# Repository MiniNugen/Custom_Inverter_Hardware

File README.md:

# Custom_Inverter_Hardware
## File Tree Should be organized like so:

PCB_Project_Name_REV1.PrjPCB  
|  Source Documents  
|  |  PCB_Project_Name_REV1.SchDOC  
|  |  PCB_Project_Name_REV1.PcbDOC  
|  |  BOM  
|  Settings  
|  Libraries  

PCB_Project_Name_REV2.PrjPCB  
|  Source Documents  
|  |  PCB_Project_Name_REV2.SchDOC  
|  |  PCB_Project_Name_REV2.PcbDOC  
|  |  BOM  
|  Settings  
|  Libraries  

PCB_Project_Name_REV3.PrjPCB  
|  Source Documents  
|  |  PCB_Project_Name_REV3.SchDOC  
|  |  PCB_Project_Name_REV3.PcbDOC  
|  |  BOM  
|  Settings  
|  Libraries

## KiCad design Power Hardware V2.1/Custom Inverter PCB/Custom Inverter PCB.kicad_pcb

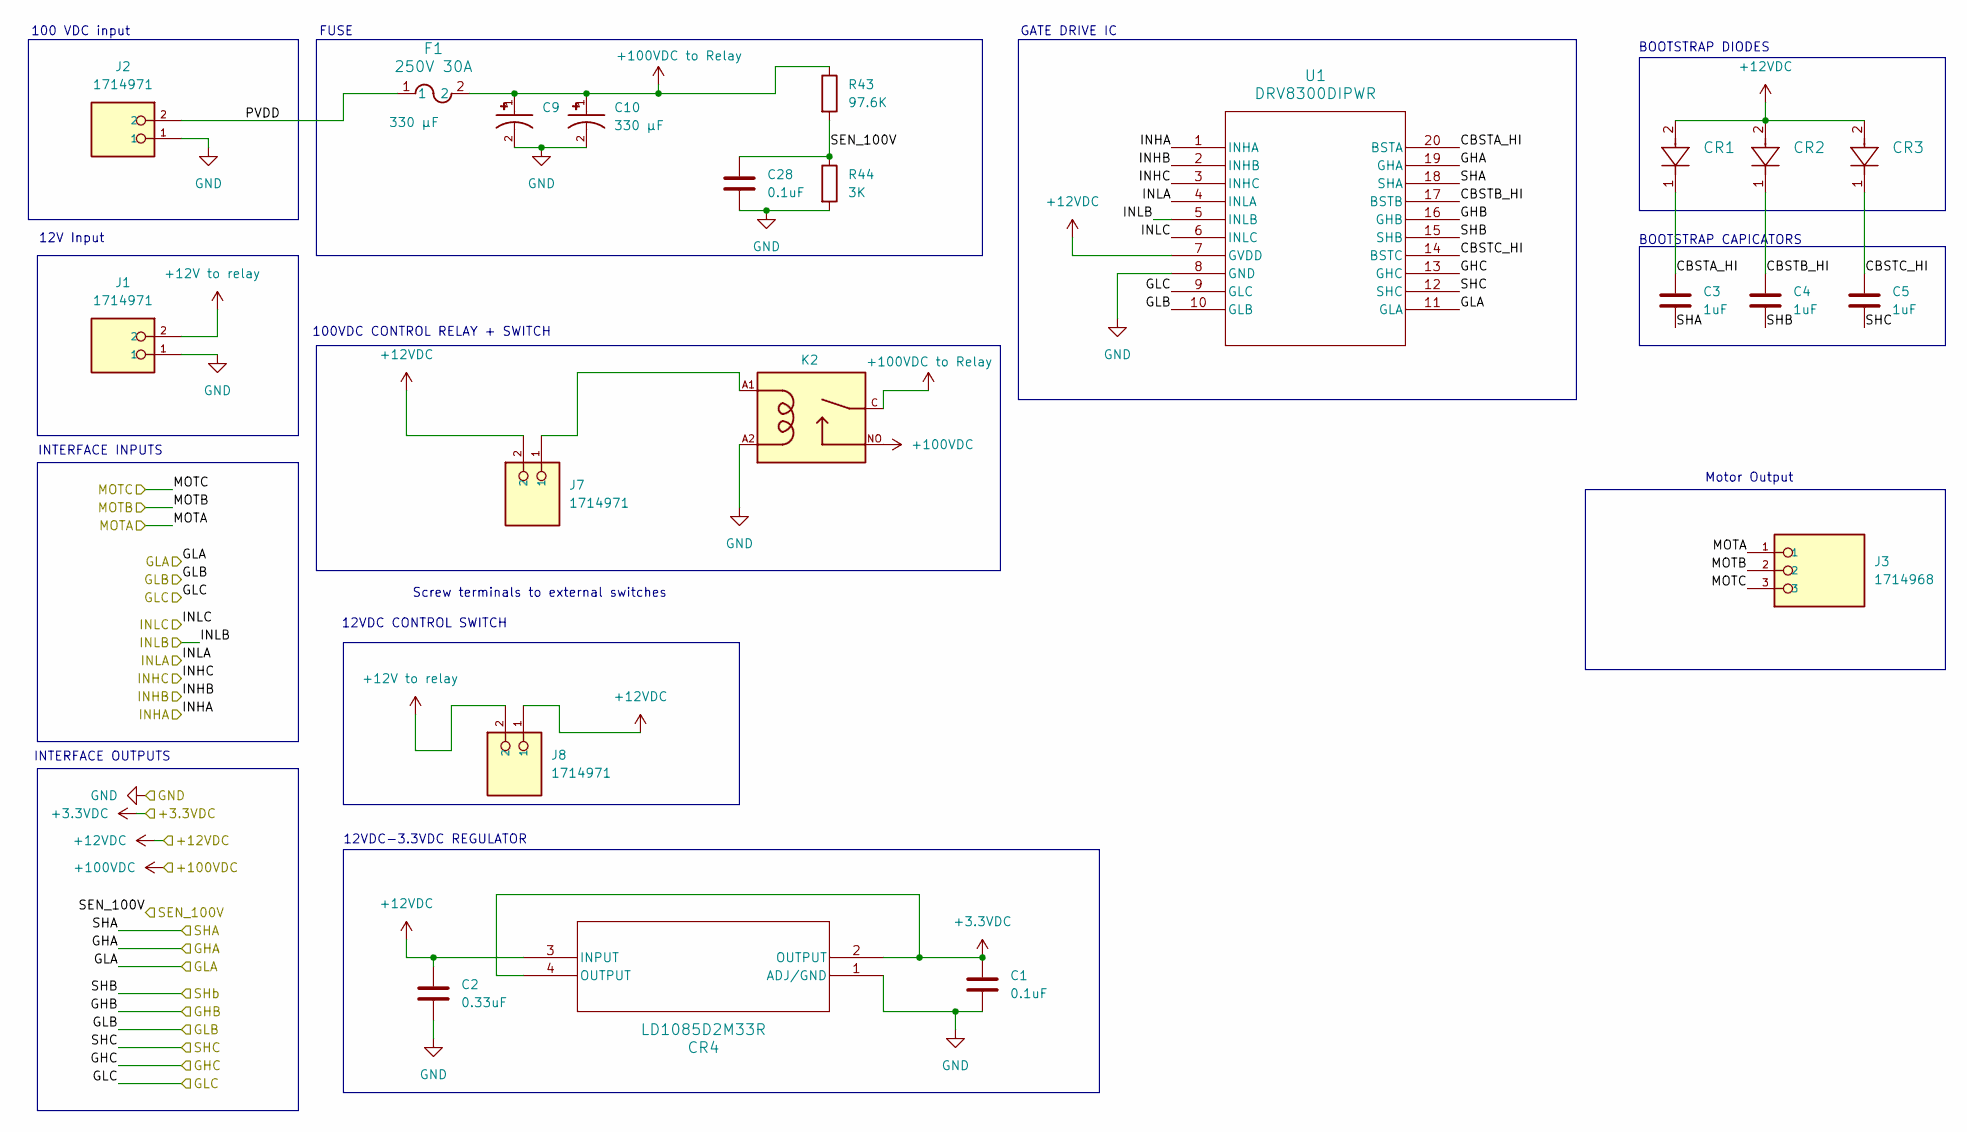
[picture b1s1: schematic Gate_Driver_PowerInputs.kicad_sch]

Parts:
C1: 0.1uF; C_0805_2012Metric; Part Number 0805ZD104KAT2A
C2: 0.33uF; C_0805_2012Metric; Part Number GRM219R71H334KA88D
C3, C4, C5: 1uF; C_0805_2012Metric; Part Number CL21B105KBFNFNE
C9, C10: 330 µF; CAP_EEVFK2A331M; PARTREV 10-Oct-19
C28: 0.1uF; C_0805_2012Metric; Part Number CC0805KRX7R9BB104
CR1, CR2, CR3: CR_SOD-323_MCC; Part Number BAV20WS-TP
CR4: LD1085D2M33R; D2PAK&slash_A_STM; Part Number LD1085D2M33R
F1: 250V 30A; FUSE_0463_LTF-M; Part Number 0463030.ER
J1, J2, J7, J8: 1714971; PHOENIX_1714971; PARTREV 26.05.2020
J3: 1714968; PHOENIX_1714968; Part Number 1714968
K2: 1-1393210-3; TE_1-1393210-3; PARTREV 0815
R43: 97.6K; R_0805_2012Metric; Part Number RC0805FR-0797K6L
R44: 3K; R_0805_2012Metric; Part Number CRG0805F3K0
U1: DRV8300DIPWR; TSSOP_0DIPWR_TEX; Part Number DRV8300DIPWR

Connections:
+3.3V: C1.1, CR4.2 (OUTPUT), CR4.4 (OUTPUT); also elsewhere on the board
+12V to relay: J1.2, J8.2
+12VDC: C2.1, CR1.2, CR2.2, CR3.2, CR4.3 (INPUT), J7.2, J8.1, U1.7 (GVDD)
+100VDC: K2.NO; also elsewhere on the board
+100VDC to Relay: C9.1, C10.1, F1.2, K2.C, R43.1
/GateDriver&Power Inputs/CBSTA_HI: C3.1, CR1.1, U1.20 (BSTA)
/GateDriver&Power Inputs/CBSTB_HI: C4.1, CR2.1, U1.17 (BSTB)
/GateDriver&Power Inputs/CBSTC_HI: C5.1, CR3.1, U1.14 (BSTC)
/GateDriver&Power Inputs/GHA: U1.19 (GHA); also elsewhere on the board
/GateDriver&Power Inputs/GHB: U1.16 (GHB); also elsewhere on the board
/GateDriver&Power Inputs/GHC: U1.13 (GHC); also elsewhere on the board
/GateDriver&Power Inputs/GLA: U1.11 (GLA); also elsewhere on the board
/GateDriver&Power Inputs/GLB: U1.10 (GLB); also elsewhere on the board
/GateDriver&Power Inputs/GLC: U1.9 (GLC); also elsewhere on the board
/GateDriver&Power Inputs/PVDD: F1.1, J2.2
/INHA: U1.1 (INHA); also elsewhere on the board
/INHB: U1.2 (INHB); also elsewhere on the board
/INHC: U1.3 (INHC); also elsewhere on the board
/INLA: U1.4 (INLA); also elsewhere on the board
/INLB: U1.5 (INLB); also elsewhere on the board
/INLC: U1.6 (INLC); also elsewhere on the board
/MOTA: J3.1; also elsewhere on the board
/MOTB: J3.2; also elsewhere on the board
/MOTC: J3.3; also elsewhere on the board
/SEN_100V: C28.1, R43.2, R44.1; also elsewhere on the board
/SHA: C3.2, U1.18 (SHA); also elsewhere on the board
/SHB: C4.2, U1.15 (SHB); also elsewhere on the board
/SHC: C5.2, U1.12 (SHC); also elsewhere on the board
GND: C1.2, C2.2, C9.2, C10.2, C28.2, CR4.1 (ADJ/GND), J1.1, J2.1, K2.A2, R44.2, U1.8 (GND); also elsewhere on the board
unnamed: J7.1, K2.A1

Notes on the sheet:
100VDC CONTROL RELAY + SWITCH
Motor Output
100 VDC input
12VDC-3.3VDC REGULATOR
12V Input
Screw terminals to external switches
FUSE
12VDC CONTROL SWITCH
GATE DRIVE IC
INTERFACE INPUTS
BOOTSTRAP DIODES
BOOTSTRAP CAPICATORS
INTERFACE OUTPUTS

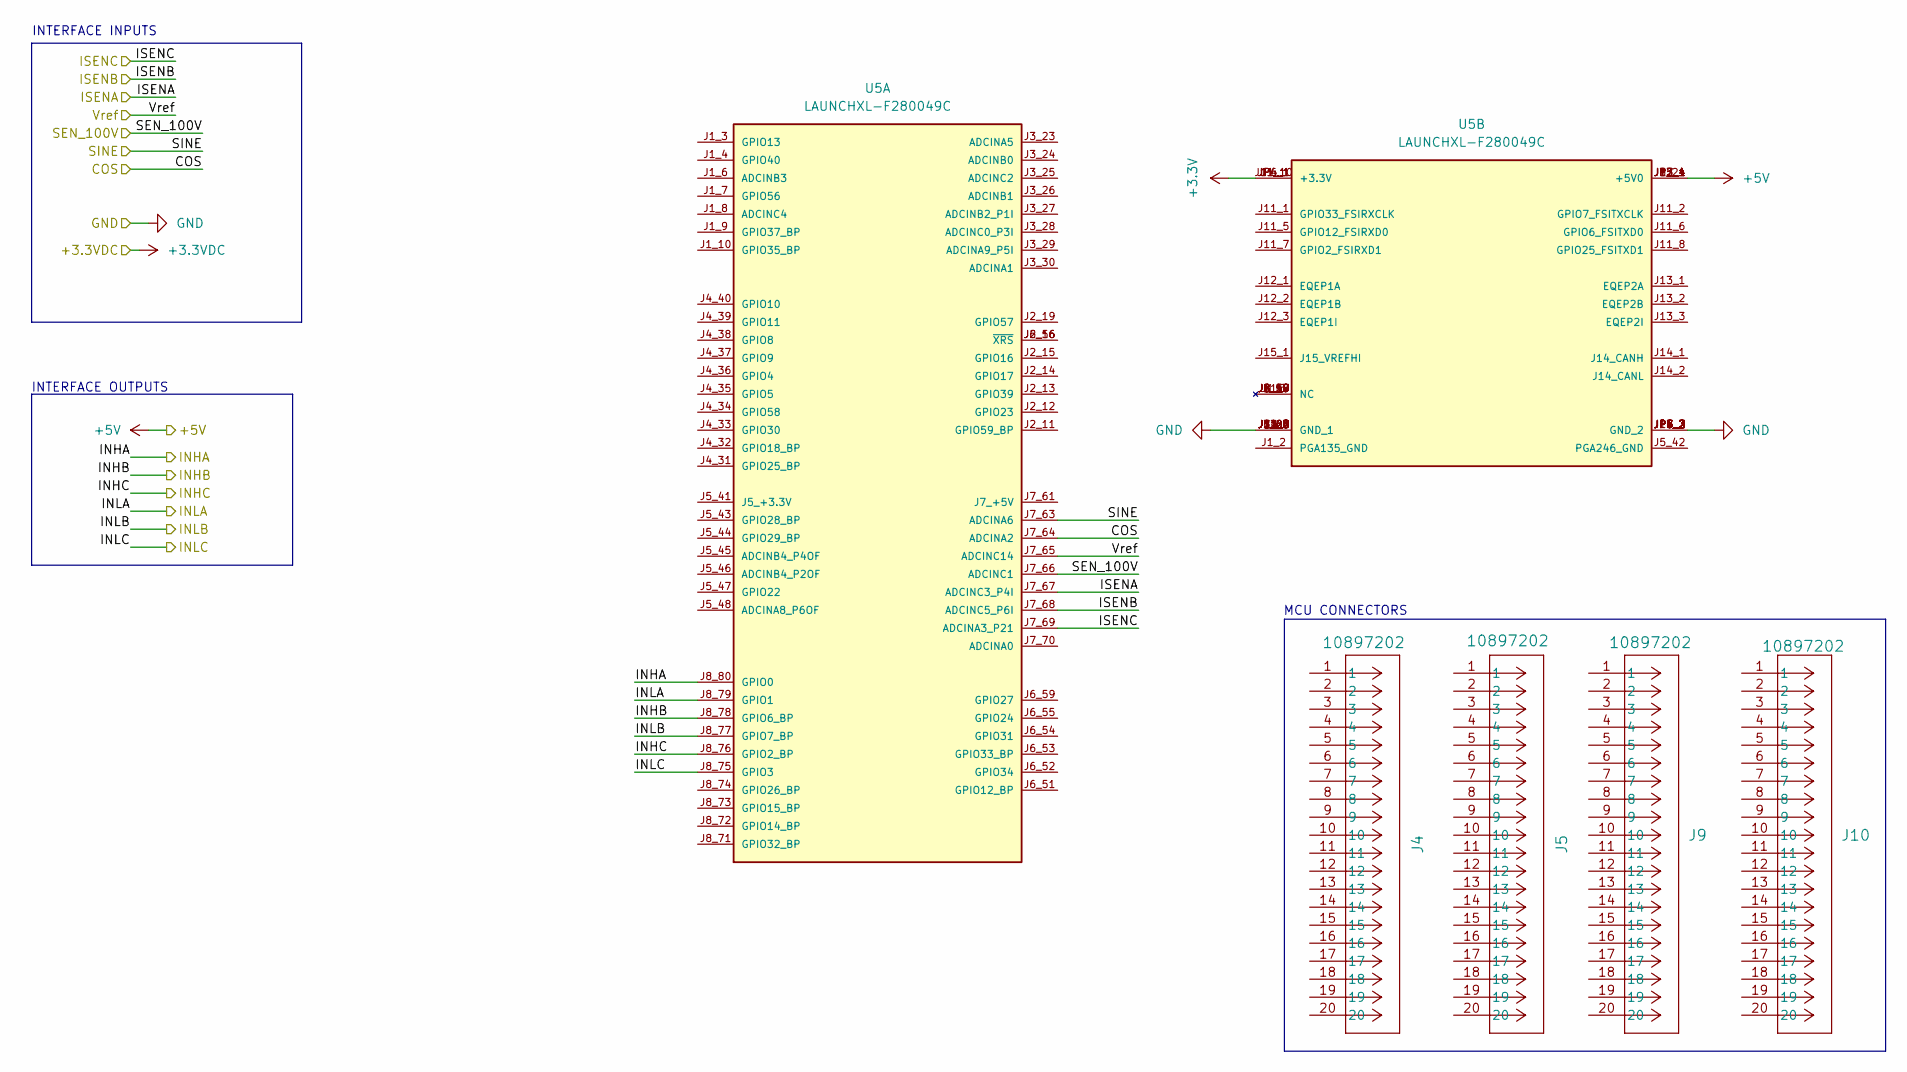
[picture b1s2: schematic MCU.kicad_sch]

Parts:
J4, J5, J9, J10: 10897202; CONN20_0010897202_MOL; Part Number 10897202
U5: LAUNCHXL-F280049C; MODULE_LAUNCHXL-F280049C; PARTREV B

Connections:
+3.3V: U5.J1_1 (+3.3V), U5.J11_10 (+3.3V), U5.JP4_1 (+3.3V), U5.JP6_1 (+3.3V); also elsewhere on the board
+5V: U5.J3_21 (+5V0), U5.J12_4 (+5V0), U5.J13_4 (+5V0), U5.JP5_1 (+5V0), U5.JP7_1 (+5V0); also elsewhere on the board
/Current sense/ISENA: U5.J7_67 (ADCINC3_P4I); also elsewhere on the board
/Current sense/ISENB: U5.J7_68 (ADCINC5_P6I); also elsewhere on the board
/Current sense/ISENC: U5.J7_69 (ADCINA3_P21); also elsewhere on the board
/Current sense/Vref: U5.J7_65 (ADCINC14); also elsewhere on the board
/Encoder Input/COS_MCU: U5.J7_64 (ADCINA2); also elsewhere on the board
/Encoder Input/SIN_MCU: U5.J7_63 (ADCINA6); also elsewhere on the board
/INHA: U5.J8_80 (GPIO0); also elsewhere on the board
/INHB: U5.J8_78 (GPIO6_BP); also elsewhere on the board
/INHC: U5.J8_76 (GPIO2_BP); also elsewhere on the board
/INLA: U5.J8_79 (GPIO1); also elsewhere on the board
/INLB: U5.J8_77 (GPIO7_BP); also elsewhere on the board
/INLC: U5.J8_75 (GPIO3); also elsewhere on the board
/SEN_100V: U5.J7_66 (ADCINC1); also elsewhere on the board
GND: U5.J2_20 (GND_1), U5.J3_22 (GND_1), U5.J6_60 (GND_1), U5.J7_62 (GND_1), U5.J11_3 (GND_1), U5.J11_4 (GND_1), U5.J12_5 (GND_1), U5.J13_5 (GND_1), U5.J14_3 (GND_1), U5.J15_2 (GND_2), U5.JP4_2 (GND_2), U5.JP4_3 (GND_2), U5.JP5_2 (GND_2), U5.JP5_3 (GND_2), U5.JP6_2 (GND_2), U5.JP6_3 (GND_2), U5.JP7_2 (GND_2), U5.JP7_3 (GND_2); also elsewhere on the board
unnamed: U5.J2_16 (~XRS), U5.J6_56 (~XRS)

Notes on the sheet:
INTERFACE INPUTS
INTERFACE OUTPUTS
MCU CONNECTORS

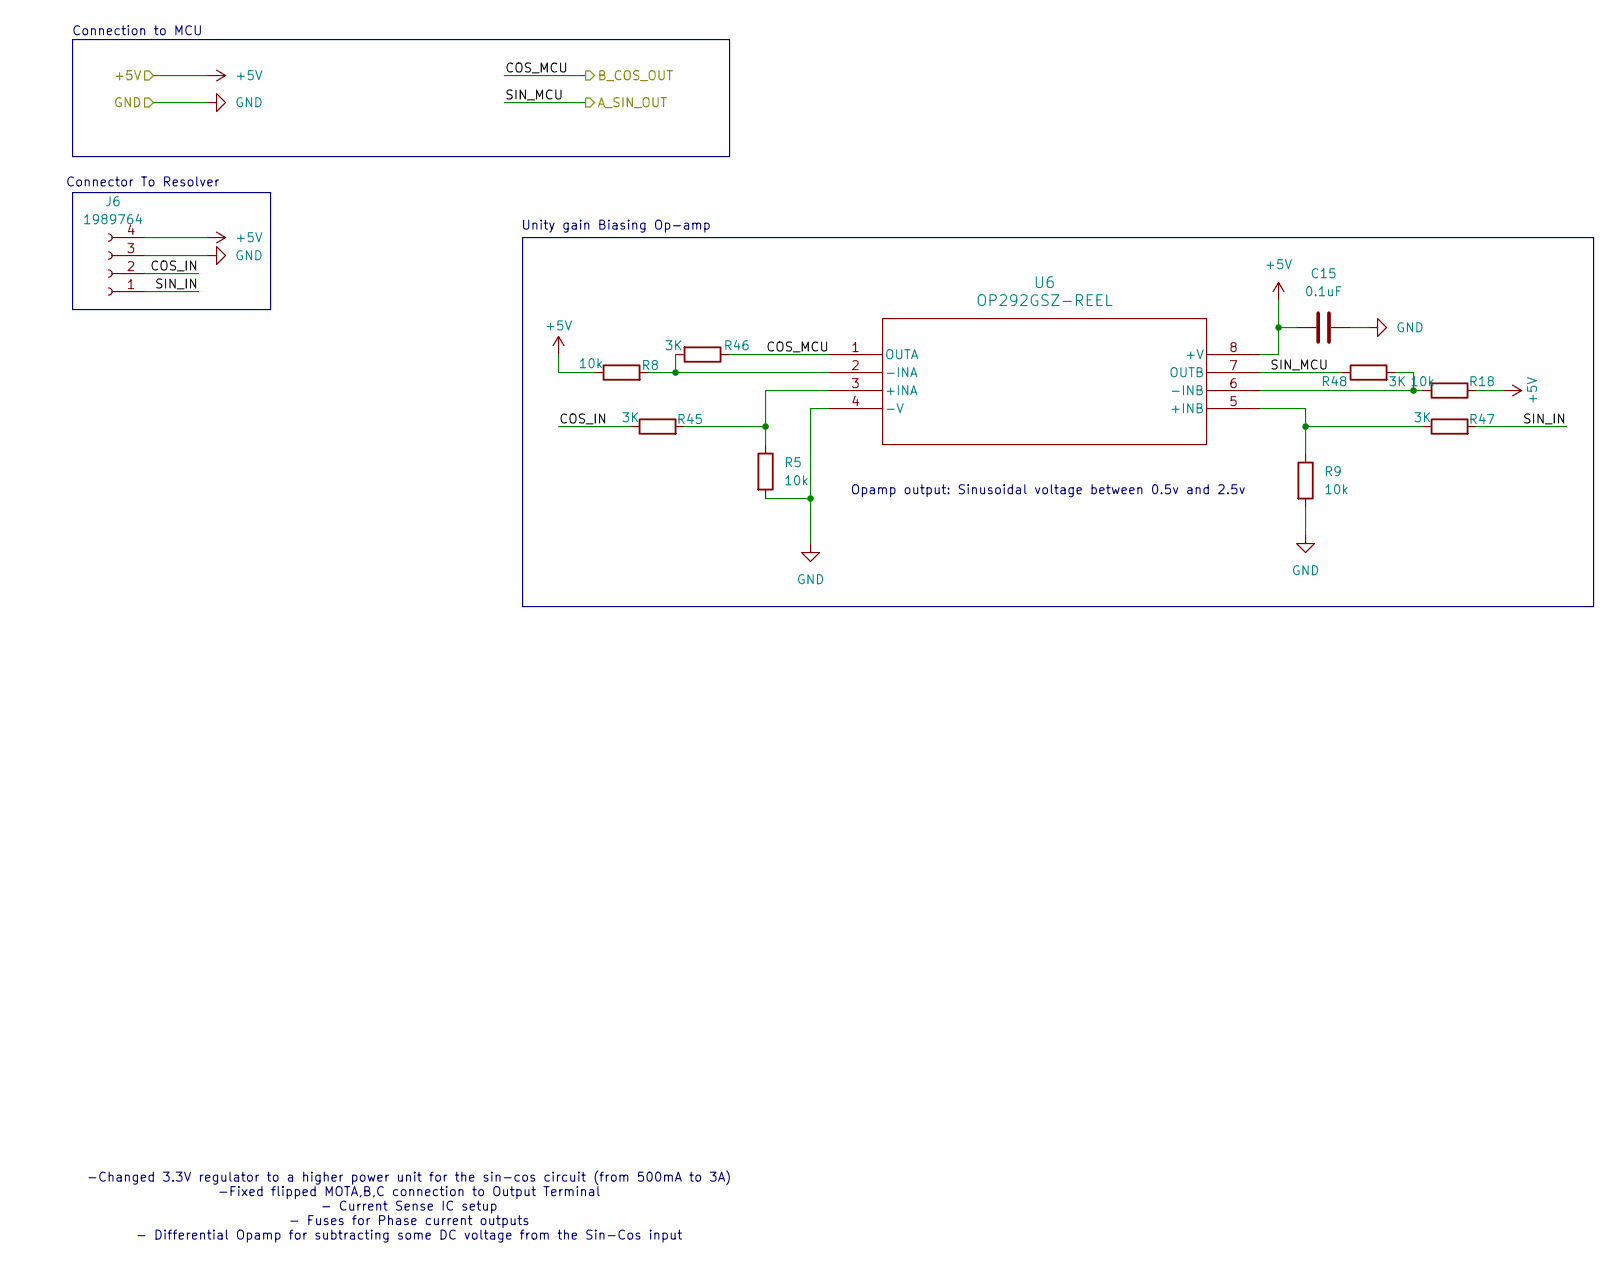
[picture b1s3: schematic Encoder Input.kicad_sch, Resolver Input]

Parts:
C15: 0.1uF; C_0805_2012Metric; Part Number 0805ZD104KAT2A
J6: 1989764; PHOENIX_1989764
R5, R9, R18: 10k; R_0805_2012Metric; Part Number ERA-6AEB103V
R8: 10k; R_0805_2012Metric
R45, R46, R47, R48: 3K; R_0805_2012Metric; Part Number CRG0805F3K0
U6: OP292GSZ-REEL; R_8_ADI

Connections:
+5V: C15.1, J6.4, R8.1, R18.1, U6.8 (+V); also elsewhere on the board
/Encoder Input/COS_IN: J6.2, R45.1
/Encoder Input/COS_MCU: R46.1, U6.1 (OUTA); also elsewhere on the board
/Encoder Input/SIN_IN: J6.1, R47.2
/Encoder Input/SIN_MCU: R48.1, U6.7 (OUTB); also elsewhere on the board
GND: C15.2, J6.3, R5.2, R9.2, U6.4 (-V); also elsewhere on the board
unnamed: R5.1, R45.2, U6.3 (+INA)
unnamed: R9.1, R47.1, U6.5 (+INB)
unnamed: R8.2, R46.2, U6.2 (-INA)
unnamed: R18.2, R48.2, U6.6 (-INB)

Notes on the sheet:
Opamp output: Sinusoidal voltage between 0.5v and 2.5v
Connector To Resolver
Unity gain Biasing Op-amp
-Changed 3.3V regulator to a higher power unit for the sin-cos circuit (from 500mA to 3A) -Fixed flipped MOTA,B,C connection to Output Terminal - Current Sense IC setup - Fuses for Phase current outputs - Differential Opamp for subtracting some DC voltage from the Sin-Cos input
Connection to MCU

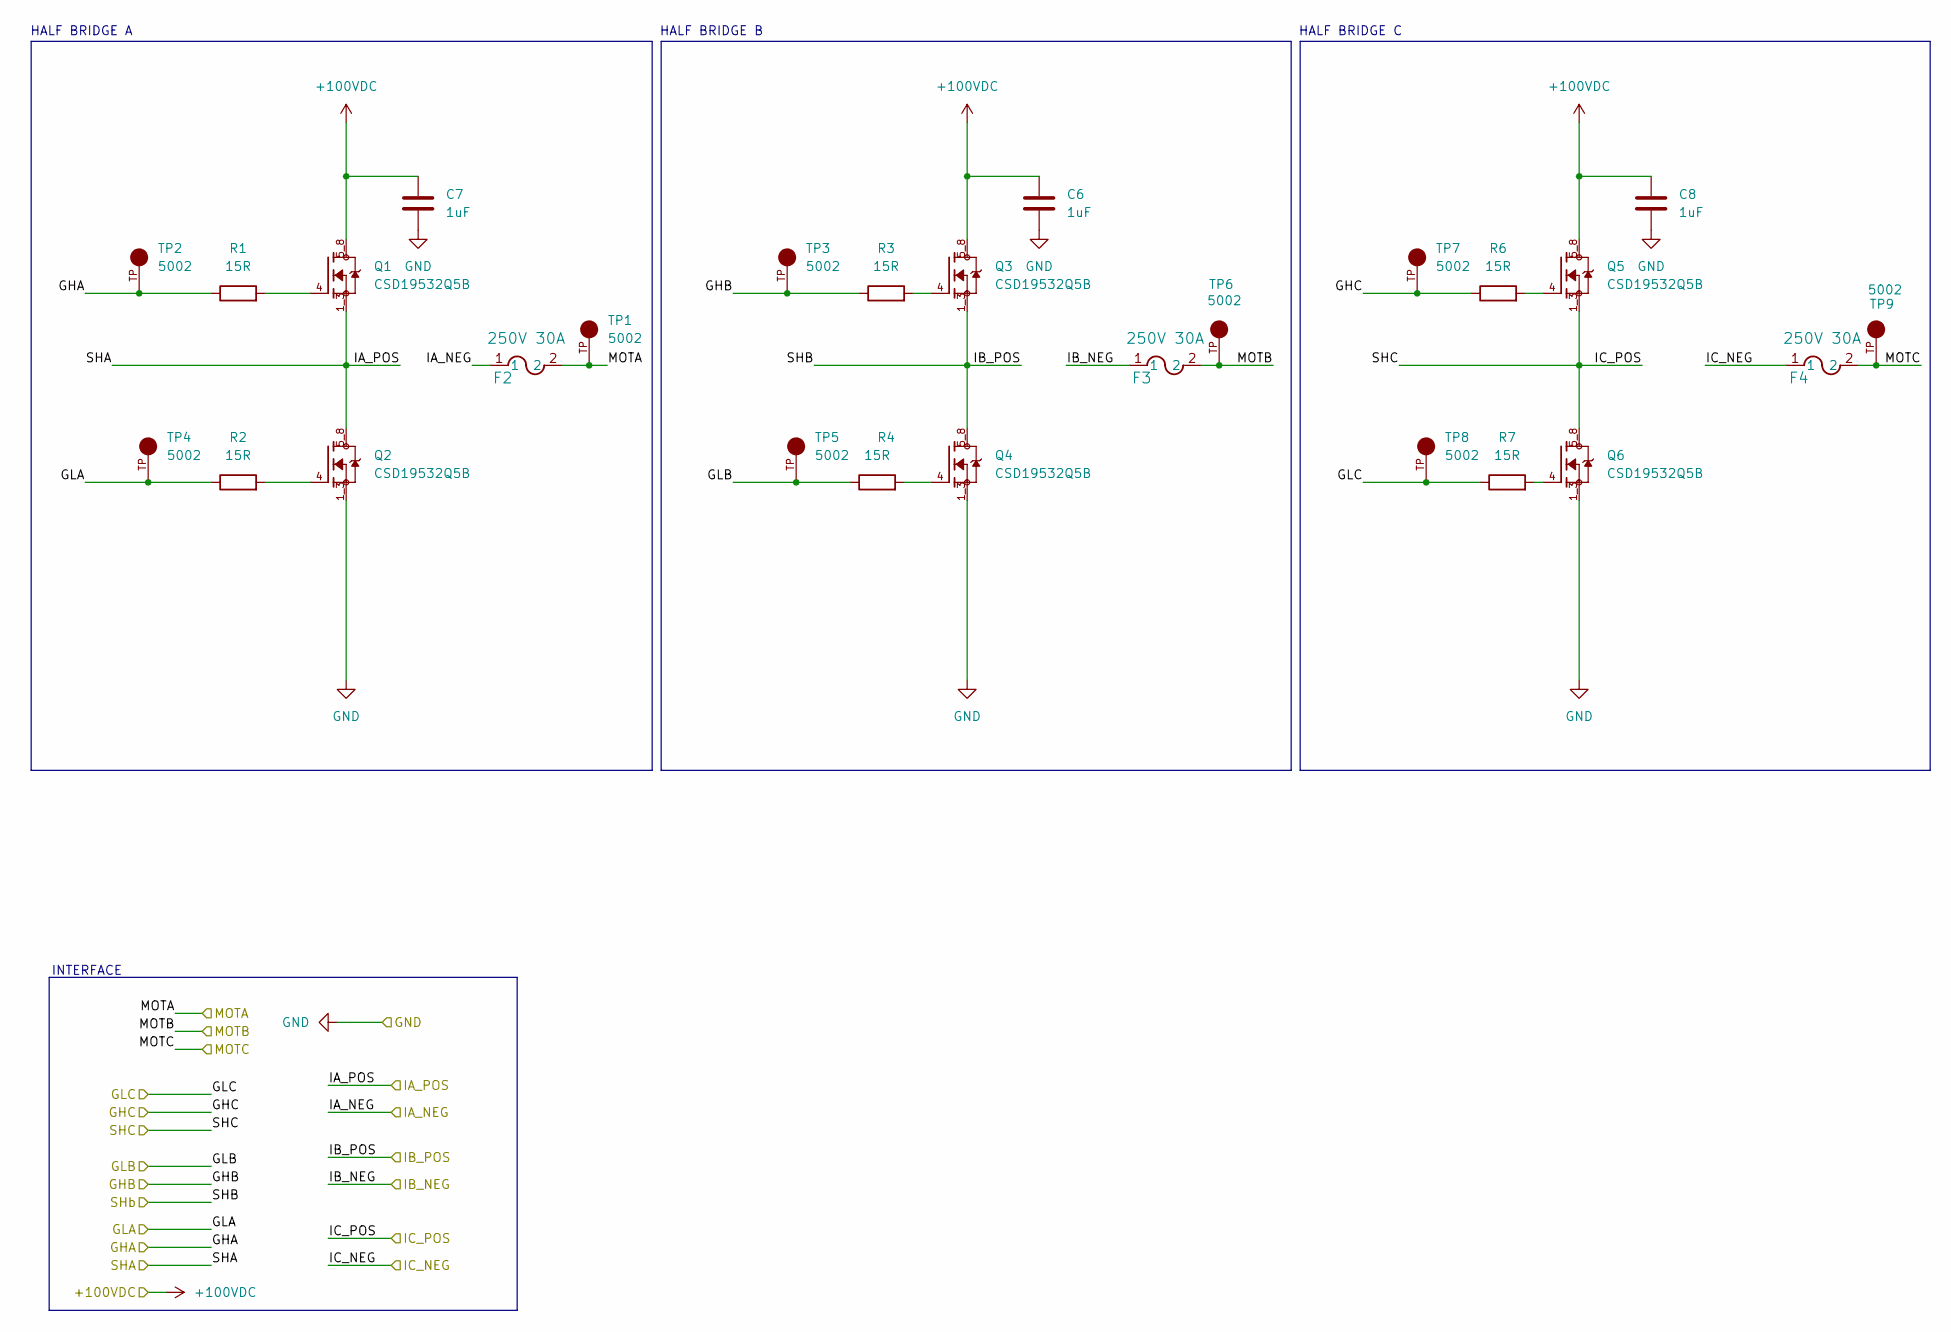
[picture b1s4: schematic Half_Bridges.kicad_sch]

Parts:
C6, C7, C8: 1uF; C_1210_3225Metric; Part Number CGA6M2X7R2A105K200AA
F2, F3, F4: 250V 30A; FUSE_0463_LTF-M; Part Number 0463030.ER
Q1, Q2, Q3, Q4, Q5, Q6: CSD19532Q5B; TRANS_CSD19532Q5B; PARTREV B
R1, R2, R3, R4, R6, R7: 15R; R_0805_2012Metric; Part Number ERJ-6GEYJ150V
TP1, TP2, TP3, TP4, TP5, TP6, TP7, TP8, TP9: 5002; KEYSTONE_5002; PARTREV H

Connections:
+100VDC: C6.1, C7.1, C8.1, Q1.5_8, Q3.5_8, Q5.5_8; also elsewhere on the board
/Current sense/IA-: F2.1; also elsewhere on the board
/Current sense/IB-: F3.1; also elsewhere on the board
/Current sense/IC-: F4.1; also elsewhere on the board
/GateDriver&Power Inputs/GHA: R1.1, TP2.TP; also elsewhere on the board
/GateDriver&Power Inputs/GHB: R3.1, TP3.TP; also elsewhere on the board
/GateDriver&Power Inputs/GHC: R6.1, TP7.TP; also elsewhere on the board
/GateDriver&Power Inputs/GLA: R2.1, TP4.TP; also elsewhere on the board
/GateDriver&Power Inputs/GLB: R4.1, TP5.TP; also elsewhere on the board
/GateDriver&Power Inputs/GLC: R7.1, TP8.TP; also elsewhere on the board
/MOTA: F2.2, TP1.TP; also elsewhere on the board
/MOTB: F3.2, TP6.TP; also elsewhere on the board
/MOTC: F4.2, TP9.TP; also elsewhere on the board
/SHA: Q1.1_3, Q2.5_8; also elsewhere on the board
/SHB: Q3.1_3, Q4.5_8; also elsewhere on the board
/SHC: Q5.1_3, Q6.5_8; also elsewhere on the board
GND: C6.2, C7.2, C8.2, Q2.1_3, Q4.1_3, Q6.1_3; also elsewhere on the board
unnamed: Q1.4, R1.2
unnamed: Q2.4, R2.2
unnamed: Q3.4, R3.2
unnamed: Q4.4, R4.2
unnamed: Q5.4, R6.2
unnamed: Q6.4, R7.2

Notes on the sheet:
HALF BRIDGE B
HALF BRIDGE A
INTERFACE
HALF BRIDGE C

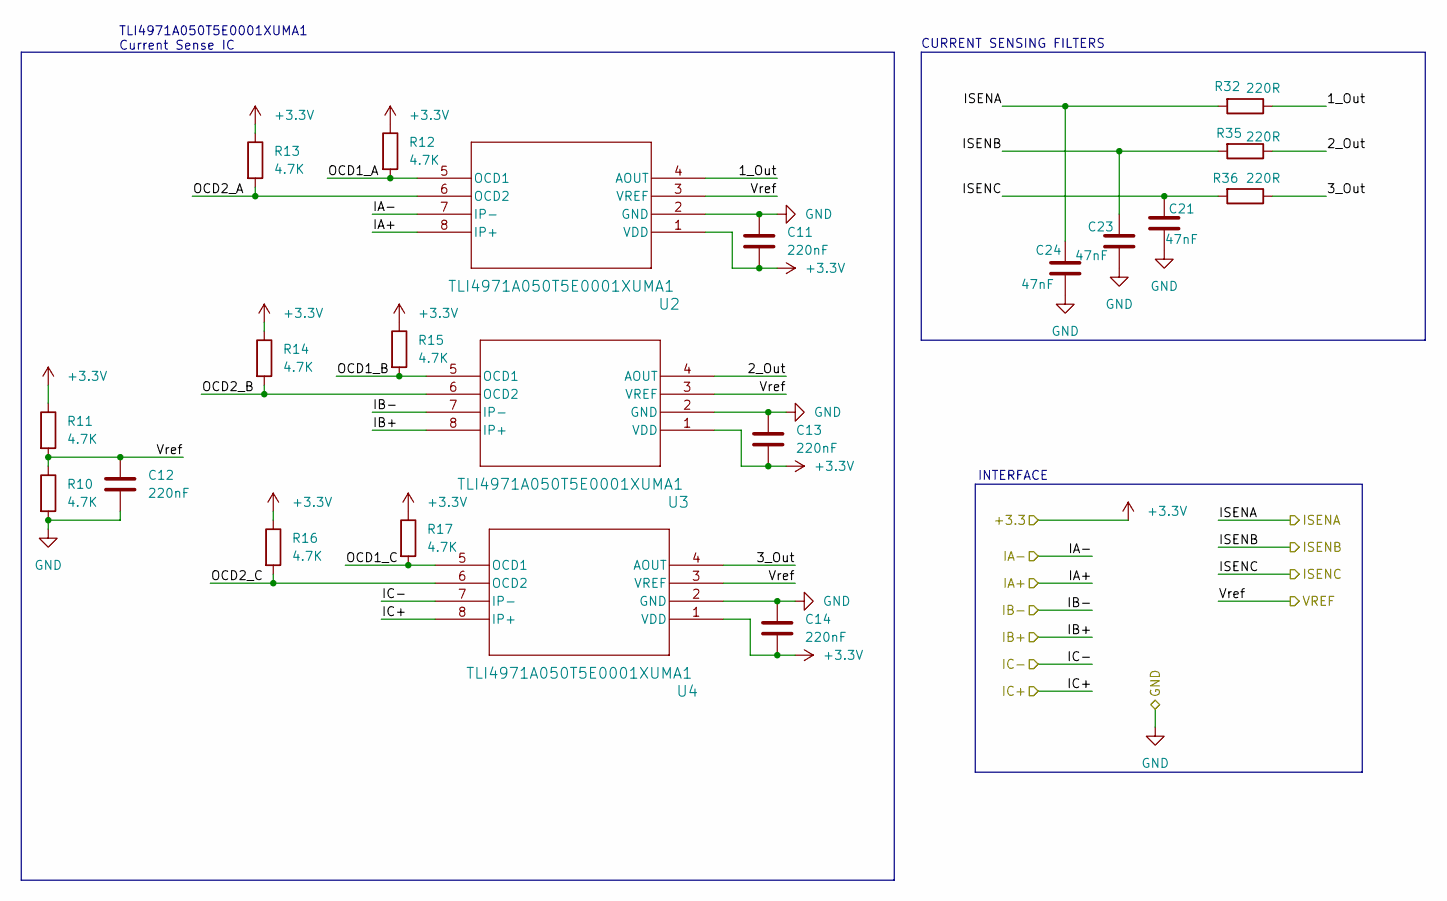
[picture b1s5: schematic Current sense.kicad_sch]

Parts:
C11, C12, C13, C14: 220nF; C_0603_1608Metric; Part Number CL21B224KAFNNNE
C21, C23, C24: 47nF; C_0805_2012Metric; Part Number C0805C473K5RACTU
R10, R11, R12, R13, R14, R15, R16, R17: 4.7K; R_0805_2012Metric; Part Number CRCW08054K70FKEAC
R32, R35, R36: 220R; R_0805_2012Metric; Part Number CRGCQ0805F220R
U2, U3, U4: TLI4971A050T5E0001XUMA1; IC_TLI4971A050T5UE0001XUMA1; Part Number TLI4971A050T5E0001XUMA1

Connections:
+3.3V: C11.2, C13.2, C14.2, R11.1, R12.1, R13.1, R14.1, R15.1, R16.1, R17.1, U2.1 (VDD), U3.1 (VDD), U4.1 (VDD); also elsewhere on the board
/Current sense/1_Out: R32.1, U2.4 (AOUT)
/Current sense/2_Out: R35.1, U3.4 (AOUT)
/Current sense/3_Out: R36.1, U4.4 (AOUT)
/Current sense/IA-: U2.7 (IP-); also elsewhere on the board
/Current sense/IB-: U3.7 (IP-); also elsewhere on the board
/Current sense/IC-: U4.7 (IP-); also elsewhere on the board
/Current sense/ISENA: C24.1, R32.2; also elsewhere on the board
/Current sense/ISENB: C23.1, R35.2; also elsewhere on the board
/Current sense/ISENC: C21.1, R36.2; also elsewhere on the board
/Current sense/OCD1_A: R12.2, U2.5 (OCD1)
/Current sense/OCD1_B: R15.2, U3.5 (OCD1)
/Current sense/OCD1_C: R17.2, U4.5 (OCD1)
/Current sense/OCD2_A: R13.2, U2.6 (OCD2)
/Current sense/OCD2_B: R14.2, U3.6 (OCD2)
/Current sense/OCD2_C: R16.2, U4.6 (OCD2)
/Current sense/Vref: C12.1, R10.1, R11.2, U2.3 (VREF), U3.3 (VREF), U4.3 (VREF); also elsewhere on the board
/SHA: U2.8 (IP+); also elsewhere on the board
/SHB: U3.8 (IP+); also elsewhere on the board
/SHC: U4.8 (IP+); also elsewhere on the board
GND: C11.1, C12.2, C13.1, C14.1, C21.2, C23.2, C24.2, R10.2, U2.2 (GND), U3.2 (GND), U4.2 (GND); also elsewhere on the board

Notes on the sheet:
CURRENT SENSING FILTERS
INTERFACE
TLI4971A050T5E0001XUMA1 Current Sense IC

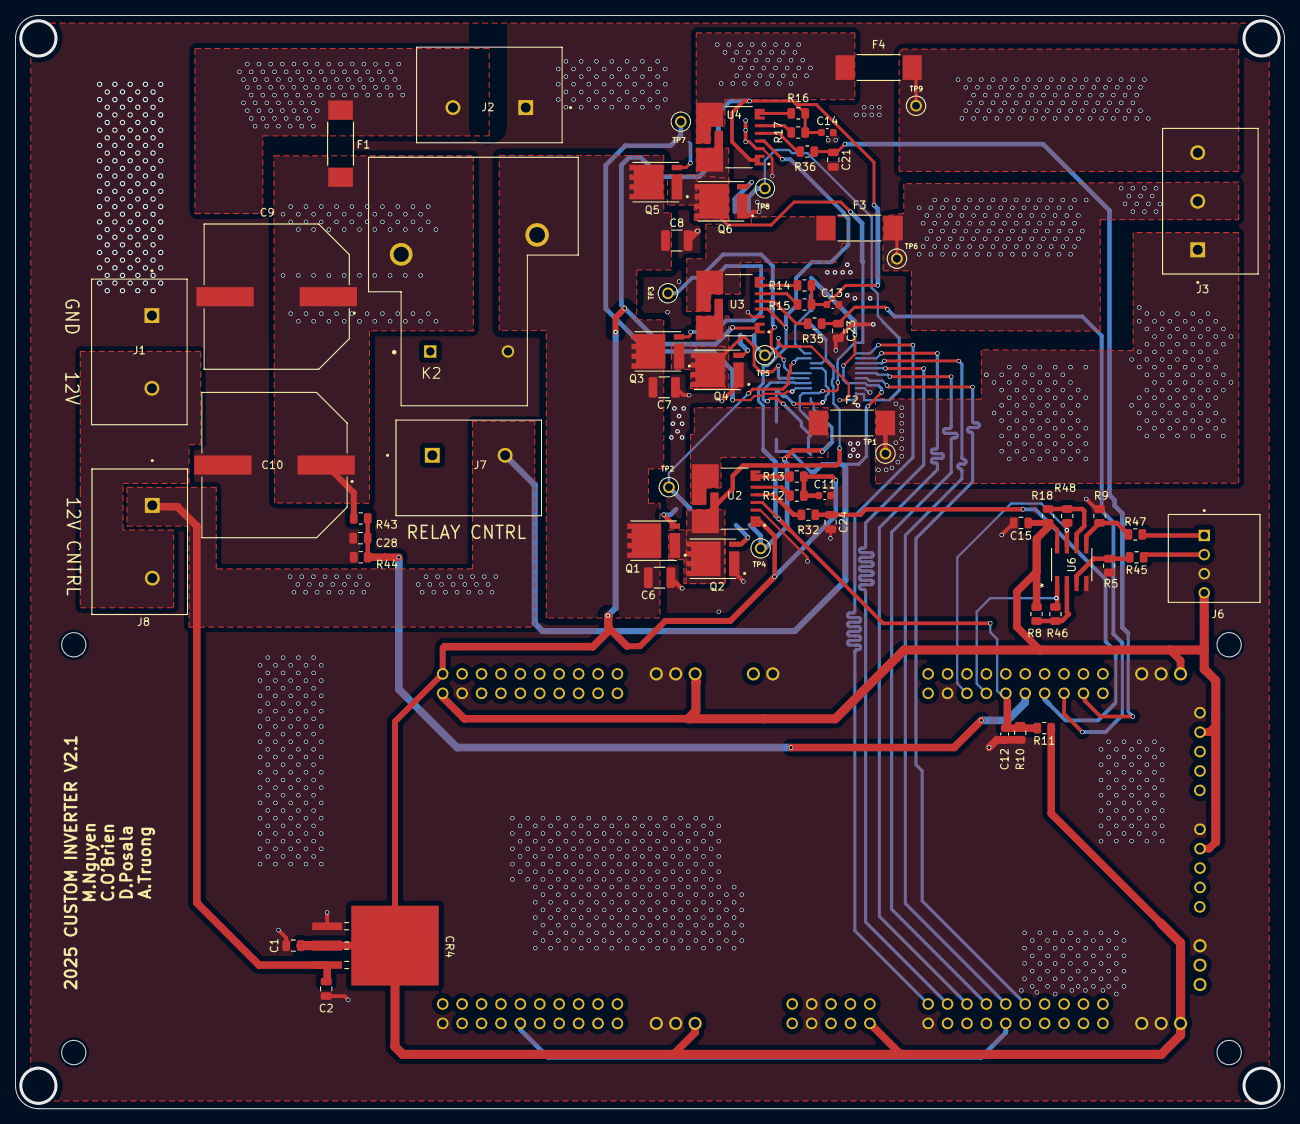
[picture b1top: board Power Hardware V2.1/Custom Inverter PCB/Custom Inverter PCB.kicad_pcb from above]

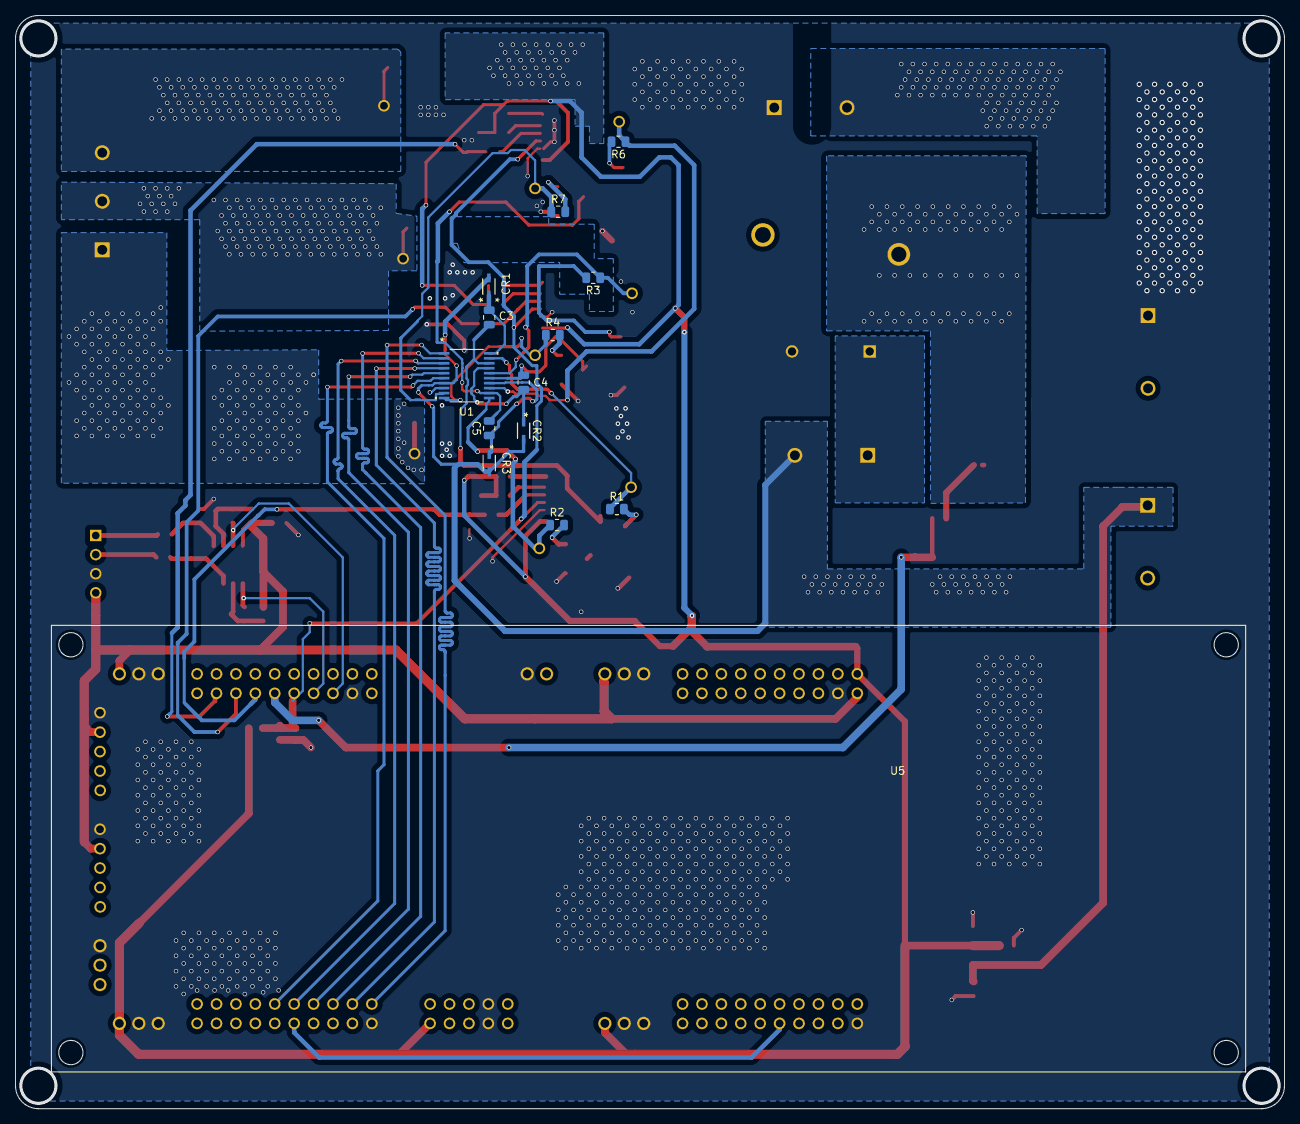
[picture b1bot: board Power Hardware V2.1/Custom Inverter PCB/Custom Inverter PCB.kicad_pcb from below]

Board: 2 copper layers, 166.0 x 143.0 mm, 82 parts (14 on the bottom side), 62 nets.

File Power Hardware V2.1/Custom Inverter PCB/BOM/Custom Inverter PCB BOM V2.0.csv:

"Reference","Value","Datasheet","Footprint","Qty","DNP","Part Number"
"C1,C15","0.1uF","https://www.digikey.ca/en/products/detail/kyocera-avx/0805ZD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","Capacitor_SMD:C_0805_2012Metric","2","","0805ZD104KAT2A"
"C2","0.33uF","https://www.digikey.ca/en/products/detail/murata-electronics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","Capacitor_SMD:C_0805_2012Metric","1","","GRM219R71H334KA88D"
"C3,C4,C5","1uF","https://www.digikey.ca/en/products/detail/samsung-electro-me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","Capacitor_SMD:C_0805_2012Metric","3","","CL21B105KBFNFNE"
"C6,C7,C8","1uF","https://www.digikey.ca/en/products/detail/tdk-corporation/CG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","Capacitor_SMD:C_1210_3225Metric","3","","CGA6M2X7R2A105K200AA"
"C9,C10","330 µF","https://industrial.panasonic.com/cdbs/www-data/pdf/RDE0000/A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","EEV_FK2A331M:CAP_EEVFK2A331M","2","","EEVFK2A331M"
"C11,C12,C13,C14","220nF","~","Capacitor_SMD:C_0603_1608Metric","4","","CL21B224KAFNNNE"
"C21,C23,C24","47nF","","Capacitor_SMD:C_0805_2012Metric","3","","C0805C473K5RACTU"
"C28","0.1uF","https://www.digikey.ca/en/products/detail/yageo/CC0805KRX7R9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","Capacitor_SMD:C_0805_2012Metric","1","","CC0805KRX7R9BB104"
"CR1,CR2,CR3","~","BAV20WS-TP","BAV20WS-TP:CR_SOD-323_MCC","3","","BAV20WS-TP"
"CR4","LD1085D2M33R","","LD1085D2M33R:D2PAK&slash_A_STM","1","","LD1085D2M33R"
"F1,F2,F3,F4","250V 30A","0463030.ER","0463030_ER:FUSE_0463_LTF-M","4","","0463030.ER"
"J1,J2,J7,J8","1714971","","1714971:PHOENIX_1714971","4","","1714971"
"J3","1714968","","PHOENIX_1714968:PHOENIX_1714968","1","","1714968"
"J4,J5,J9,J10","10897202","10897202","CONN20_0010897202_MOL","4","","10897202"
"J6","1989764","~","PHOENIX_1989764:PHOENIX_1989764","1","","1989764"
"K2","1-1393210-3","","T9AS1D12_12:TE_1-1393210-3","1","","T9AS1D12-12"
"Q1,Q2,Q3,Q4,Q5,Q6","CSD19532Q5B","","CSD19532Q5B:TRANS_CSD19532Q5B","6","","CSD19532Q5B"
"R1,R2,R3,R4,R6,R7","15R","https://www.digikey.ca/en/products/detail/panasonic-electron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","Resistor_SMD:R_0805_2012Metric","6","","ERJ-6GEYJ150V"
"R5,R8,R9,R18","10k","https://industrial.panasonic.com/cdbs/www-data/pdf/RDM0000/A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","Resistor_SMD:R_0805_2012Metric","4","","ERA-6AEB103V"
"R10,R11,R12,R13,R14,R15,R16,R17","4.7K","~","Resistor_SMD:R_0805_2012Metric","8","","CRCW08054K70FKEAC"
"R32,R35,R36","220R","","Resistor_SMD:R_0805_2012Metric","3","","CRGCQ0805F220R"
"R43","97.6K","https://www.digikey.ca/en/products/detail/yageo/RC0805FR-079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","Resistor_SMD:R_0805_2012Metric","1","","RC0805FR-0797K6L"
"R44,R45,R46,R47,R48","3K","https://www.digikey.ca/en/products/detail/te-connectivity-pa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","Resistor_SMD:R_0805_2012Metric","5","","CRG0805F3K0"
"TP1,TP2,TP3,TP4,TP5,TP6,TP7,TP8,TP9","5002","","5002:KEYSTONE_5002","9","","5002"
"U1","DRV8300DIPWR","DRV8300DIPWR","DRV8300DIPWR:TSSOP_0DIPWR_TEX","1","","DRV8300DIPWR"
"U2,U3,U4","TLI4971A050T5E0001XUMA1","TLI4971A050T5E0001XUMA1","TLI4971A:IC_TLI4971A050T5UE0001XUMA1","3","","TLI4971A050T5E0001XUMA1"
"U5","LAUNCHXL-F280049C","","LAUNCHXL-F280049C:MODULE_LAUNCHXL-F280049C","1","","LAUNCHXL-F280049C"
"U6","OP292GSZ-REEL","OP292GSZ-REEL","R_8_ADI","1","","OP292GSZ-REEL"
